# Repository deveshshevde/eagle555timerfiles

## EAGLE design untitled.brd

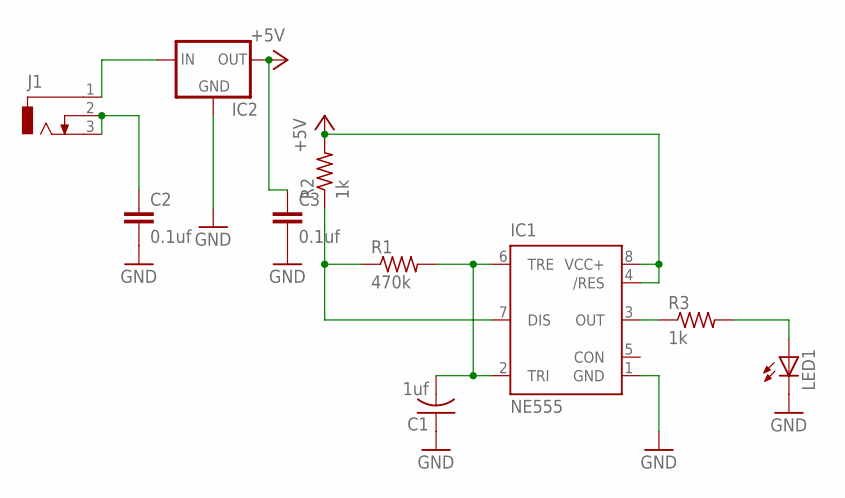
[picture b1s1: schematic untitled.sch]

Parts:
C1: 1uf; C025-024X044
C2, C3: 0.1uf; C025-030X050
IC1: NE555; DIL-08
IC2: 78XXS
J1: DCJ0303
LED1: LED5MM
R1: 470k; 0309/12
R2, R3: 1k; 0309/12

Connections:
+5V: C3.1, IC1.4 (/RES), IC1.8 (VCC+), IC2.OUT, R2.2
GND: C1.1, C2.2, C3.2, IC1.1 (GND), IC2.GND, LED1.K (C)
unnamed: C1.2, IC1.2 (TRI), IC1.6 (TRE), R1.2
unnamed: IC1.7 (DIS), R1.1, R2.1
unnamed: IC1.3 (OUT), R3.1
unnamed: LED1.A, R3.2
unnamed: C2.1, J1.2, J1.3
unnamed: IC2.IN, J1.1

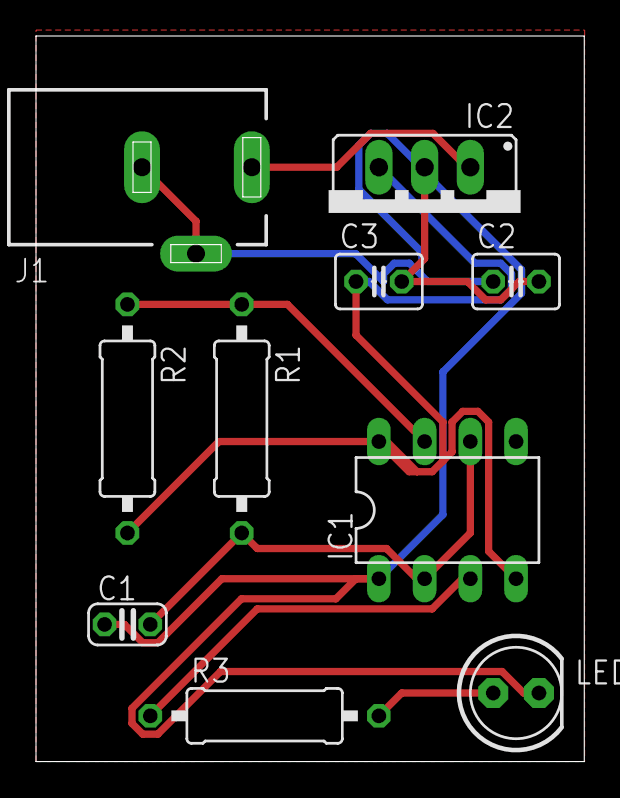
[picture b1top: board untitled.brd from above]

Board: 2 copper layers, 30.5 x 40.3 mm, 10 parts (0 on the bottom side), 8 nets.

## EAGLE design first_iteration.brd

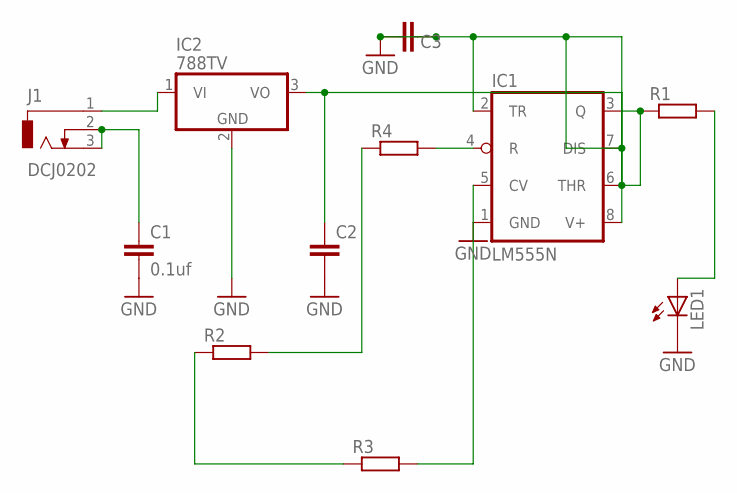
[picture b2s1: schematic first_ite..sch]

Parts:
C1: 0.1uf; C025-024X044
C2, C3: C-EU025-024X044; C025-024X044
IC1: LM555N; DIL08-ROUND
IC2: 788TV; TO220V
J1: DCJ0202
LED1: LED5MM
R1, R2, R3, R4: R-EU_0204/7; 0204/7

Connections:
GND: C1.2, C2.2, C3.1, C3.2, IC1.1 (GND), IC1.2 (TR), IC1.3 (Q), IC1.6 (THR), IC1.7 (DIS), IC2.2 (GND), LED1.K (C), R1.1
unnamed: C1.1, J1.2, J1.3
unnamed: IC2.1 (VI), J1.1
unnamed: C2.1, IC1.8 (V+), IC2.3 (VO)
unnamed: LED1.A, R1.2
unnamed: IC1.4 (R), R4.2
unnamed: R2.2, R4.1
unnamed: R2.1, R3.1
unnamed: IC1.5 (CV), R3.2

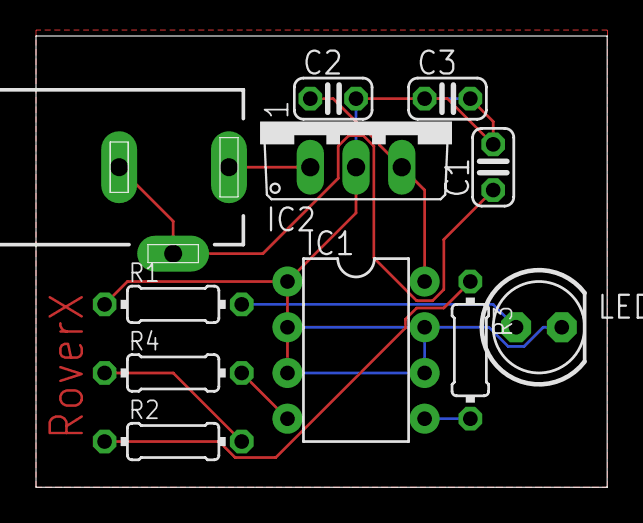
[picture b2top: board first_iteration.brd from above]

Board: 2 copper layers, 31.7 x 25.1 mm, 11 parts (0 on the bottom side), 9 nets.
